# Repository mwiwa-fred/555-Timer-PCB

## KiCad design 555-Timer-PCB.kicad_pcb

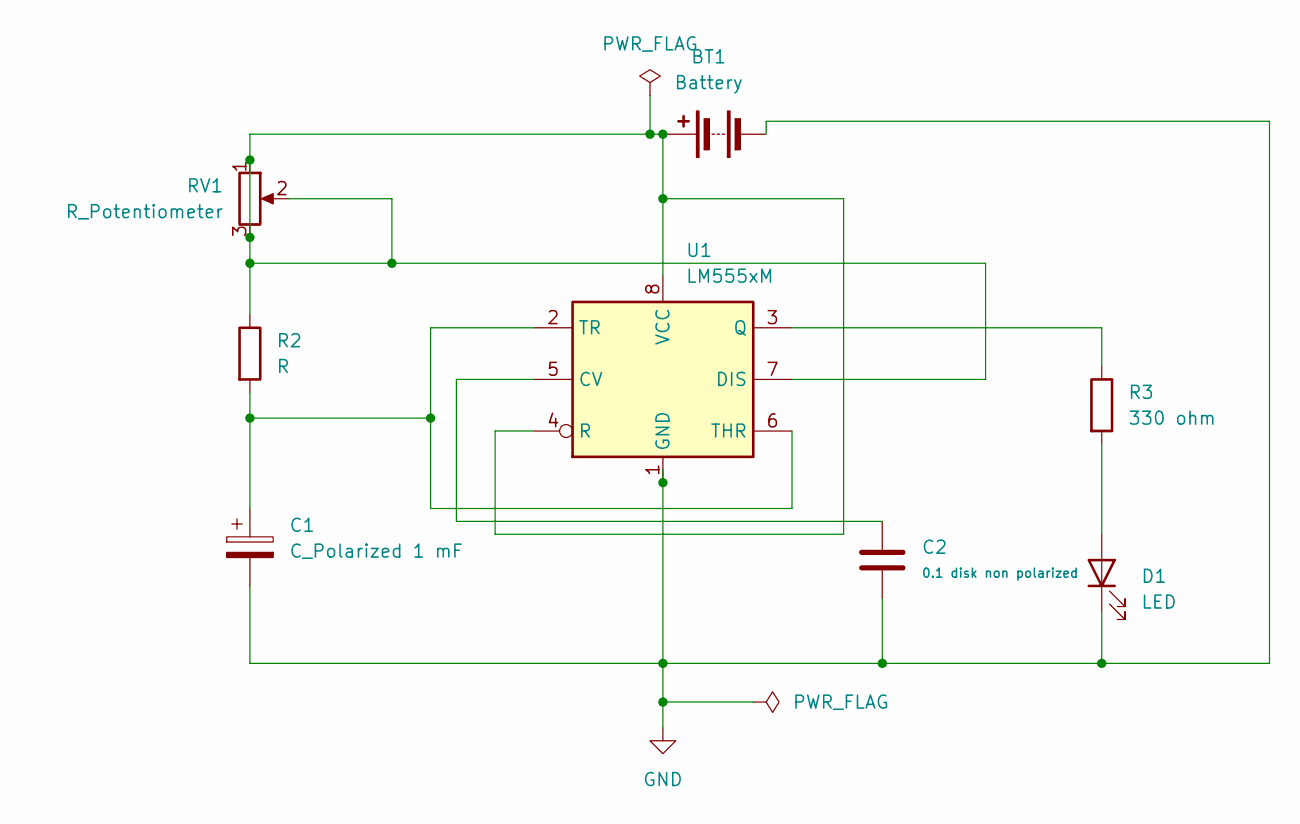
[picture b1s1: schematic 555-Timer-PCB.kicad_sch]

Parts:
BT1: Battery; BatteryHolder_Keystone_2468_2xAAA
C1: C_Polarized 1 mF; CP_EIA-1608-08_AVX-J_Pad1.25x1.05mm_HandSolder
C2: 0.1 disk non polarized; C_Axial_L3.8mm_D2.6mm_P10.00mm_Horizontal
D1: LED; LED_D3.0mm
R2: R; R_Axial_DIN0204_L3.6mm_D1.6mm_P5.08mm_Vertical
R3: 330 ohm; R_Axial_DIN0204_L3.6mm_D1.6mm_P5.08mm_Horizontal
RV1: R_Potentiometer; Potentiometer_ACP_CA6-H2,5_Horizontal
U1: LM555xM; SOIC-8_3.9x4.9mm_P1.27mm

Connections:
GND: BT1.2 (-), C1.2, C2.2, D1.1 (K), U1.1 (GND)
unnamed: BT1.1 (+), R2.1, RV1.1, RV1.2, RV1.3, U1.4 (R), U1.7 (DIS), U1.8 (VCC)
unnamed: D1.2 (A), R3.2
unnamed: C2.1, U1.5 (CV)
unnamed: R3.1, U1.3 (Q)
unnamed: C1.1, R2.2, U1.2 (TR), U1.6 (THR)

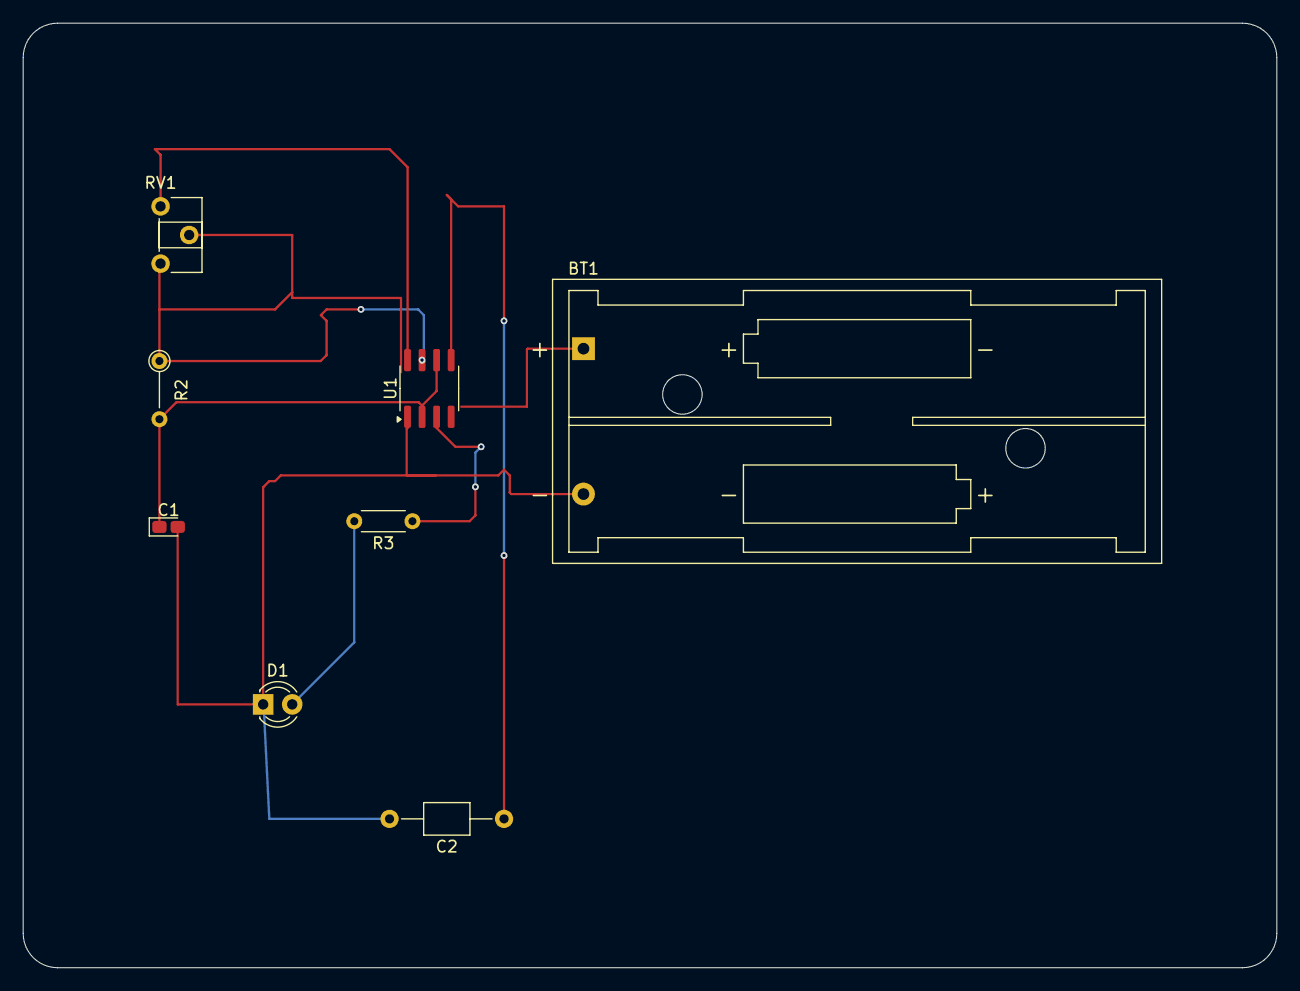
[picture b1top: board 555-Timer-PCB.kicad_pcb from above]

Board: 2 copper layers, 109.5 x 82.5 mm, 8 parts (0 on the bottom side), 6 nets.
